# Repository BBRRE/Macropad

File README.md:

**Initial render of the Macropad**

**Schematic and PCB wiring**

**Ordered the PCB from JLCPCB **

Waiting for extra parts.<br>
Soldering and firmware Completed, Will update the repo soon with a better read me and upload the firmware

V2 design: https://imgur.com/a/PmoHiHx

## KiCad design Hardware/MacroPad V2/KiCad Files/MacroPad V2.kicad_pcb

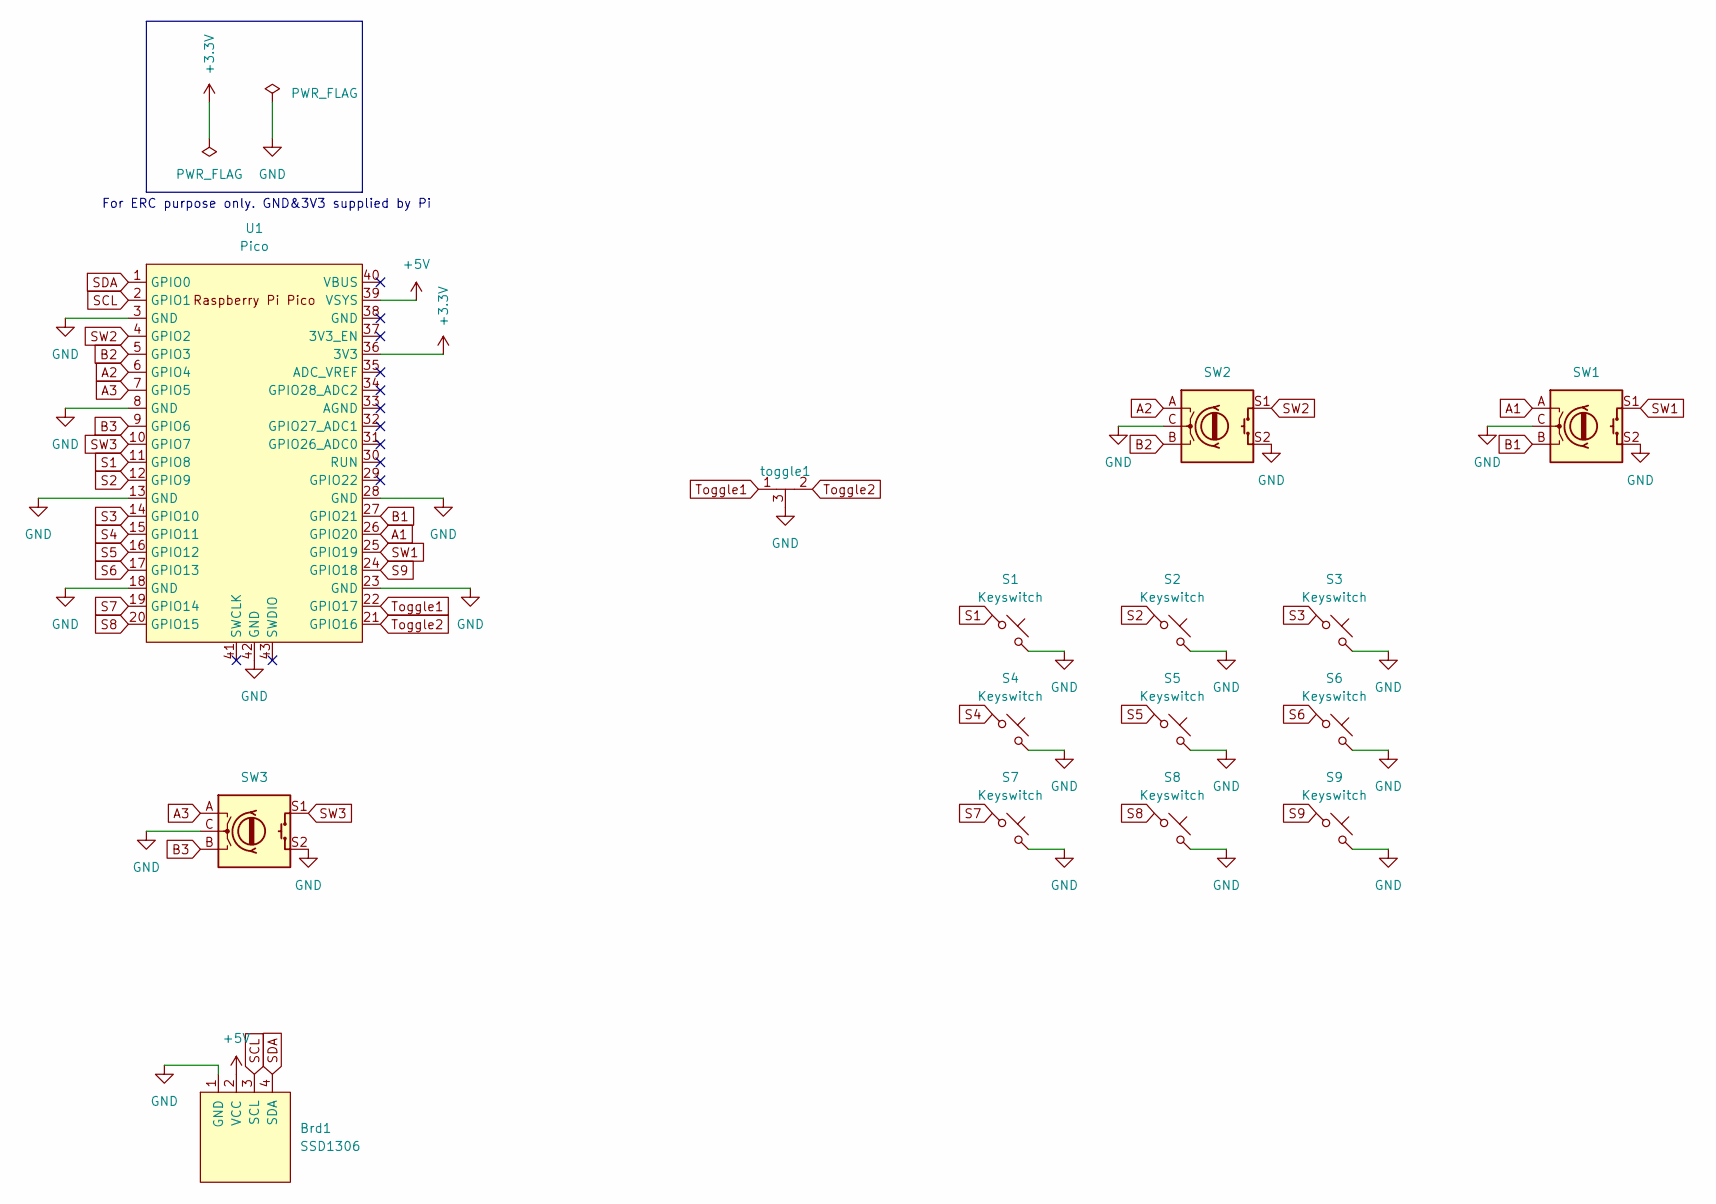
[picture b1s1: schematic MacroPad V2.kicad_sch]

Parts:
Brd1: SSD1306; 128x64OLED
S1, S2, S3, S4, S5, S6, S7, S8, S9: Keyswitch; MX_PCB_1.00u
SW1, SW2, SW3: RotaryEncoder_Switch; RotaryEncoder_Alps_EC11E-Switch_Vertical_H20mm
U1: Pico; RPi_Pico_SMD_TH
toggle1: Toggle on-off-on

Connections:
+3.3V: U1.36 (3V3)
+5V: Brd1.2 (VCC), U1.39 (VSYS)
A1: SW1.A, U1.26 (GPIO20)
A2: SW2.A, U1.6 (GPIO4)
A3: SW3.A, U1.7 (GPIO5)
B1: SW1.B, U1.27 (GPIO21)
B2: SW2.B, U1.5 (GPIO3)
B3: SW3.B, U1.9 (GPIO6)
GND: Brd1.1 (GND), S1.2, S2.2, S3.2, S4.2, S5.2, S6.2, S7.2, S8.2, S9.2, SW1.C, SW1.S2, SW2.C, SW2.S2, SW3.C, SW3.S2, U1.3 (GND), U1.8 (GND), U1.13 (GND), U1.18 (GND), U1.23 (GND), U1.28 (GND), U1.42 (GND), toggle1.3
S1: S1.1, U1.11 (GPIO8)
S2: S2.1, U1.12 (GPIO9)
S3: S3.1, U1.14 (GPIO10)
S4: S4.1, U1.15 (GPIO11)
S5: S5.1, U1.16 (GPIO12)
S6: S6.1, U1.17 (GPIO13)
S7: S7.1, U1.19 (GPIO14)
S8: S8.1, U1.20 (GPIO15)
S9: S9.1, U1.24 (GPIO18)
SCL: Brd1.3 (SCL), U1.2 (GPIO1)
SDA: Brd1.4 (SDA), U1.1 (GPIO0)
SW1: SW1.S1, U1.25 (GPIO19)
SW2: SW2.S1, U1.4 (GPIO2)
SW3: SW3.S1, U1.10 (GPIO7)
Toggle1: U1.22 (GPIO17), toggle1.1
Toggle2: U1.21 (GPIO16), toggle1.2

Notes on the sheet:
For ERC purpose only. GND&3V3 supplied by Pi

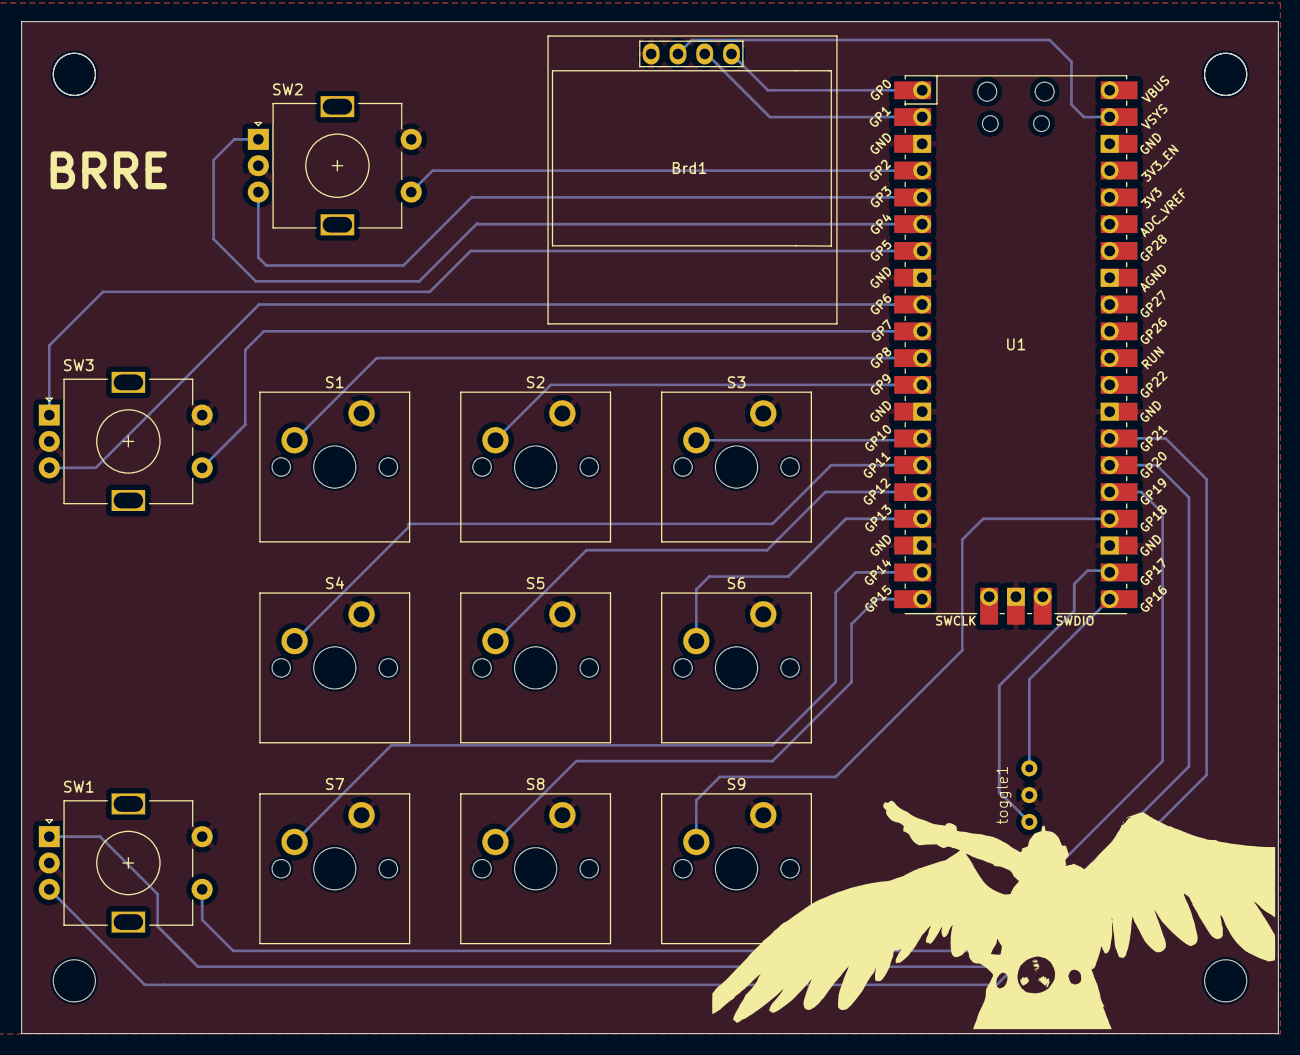
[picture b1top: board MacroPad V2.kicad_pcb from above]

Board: 2 copper layers, 119.2 x 96.0 mm, 15 parts (0 on the bottom side), 24 nets.

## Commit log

2023-12-21 Initial schematic
    3 by 3 keyboard matrix, 3 rotary encoder and a switch
2023-12-21 3D model
2023-12-22 New schematic
    Added a small display, rewired the keys to be individually wired, might change the switch I'm using since its way too stiff
2023-12-22 Redid the schematic should be finished
2023-12-22 Electric test work
2023-12-22 Turns out I didn't pull up resistors for the rotary encoder
    The pi pico has a PULL_UP for this lol
2023-12-22 last schematic update????
    Oled screen now hooked up on 5V
2023-12-23 Finall rendistionq
    hopefully
2023-12-23 Final PCB design
    Image left
2023-12-23 Final version and ready to send
    Yipee
2023-12-24 Changes some stuff
    Cant remember
2023-12-25 Working on a v2
2023-12-25 Completed V2 and organised fiels
    I rewired the PCB to avoid pins going through each other. YIPEE
2023-12-25 Cleaned up the PCB Wiring
2023-12-25 Rewired to avoid pins
2023-12-25 Gerber
2024-12-04 Restructer and added Firmware
2024-12-04 Create Hardware
2025-01-16 Screeen sizee
